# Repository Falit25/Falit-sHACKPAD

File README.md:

# Falit'sHackpad – 10-Key Macro Pad

Falit's Hackpad is a custom 10-key macro pad built using a XIAO RP2040 DIP board.
It uses KMK firmware (CircuitPython) and is designed for productivity shortcuts like launching apps, switching desktops, and system controls.

---

## Features

* 10 mechanical keys
* 4× SK6812 RGB LEDs
* XIAO RP2040 DIP controller
* USB-C connection
* KMK firmware
* Custom 3D-printed case
* App-launch and system macros (Windows)

---

## Hardware

* Controller: Seeed XIAO RP2040 DIP
* Switches: MX-style mechanical switches
* LEDs: SK6812 Mini (NeoPixel-compatible)
* PCB: Custom KiCad design
* Case: Custom Fusion 360 model
* Connection: USB-C

---

## Firmware

Firmware is written using **KMK** and runs on **CircuitPython**.

### Steps

1. Install CircuitPython on XIAO RP2040
2. Copy the KMK firmware folder to the board
3. Upload `main.py` to the CIRCUITPY drive
4. Reboot the board

---

## Notes

* App-launch shortcuts use AutoHotkey for reliability
* LEDs are driven from GPIO3
* Keys are connected using direct GPIO pins
* Modify `main.py` to change macros or lighting behavior

---

## License

This project is for personal and educational use.

---

## Author

Mahi
B.Tech Student – VIT Bhopal
Specialization: AI & ML

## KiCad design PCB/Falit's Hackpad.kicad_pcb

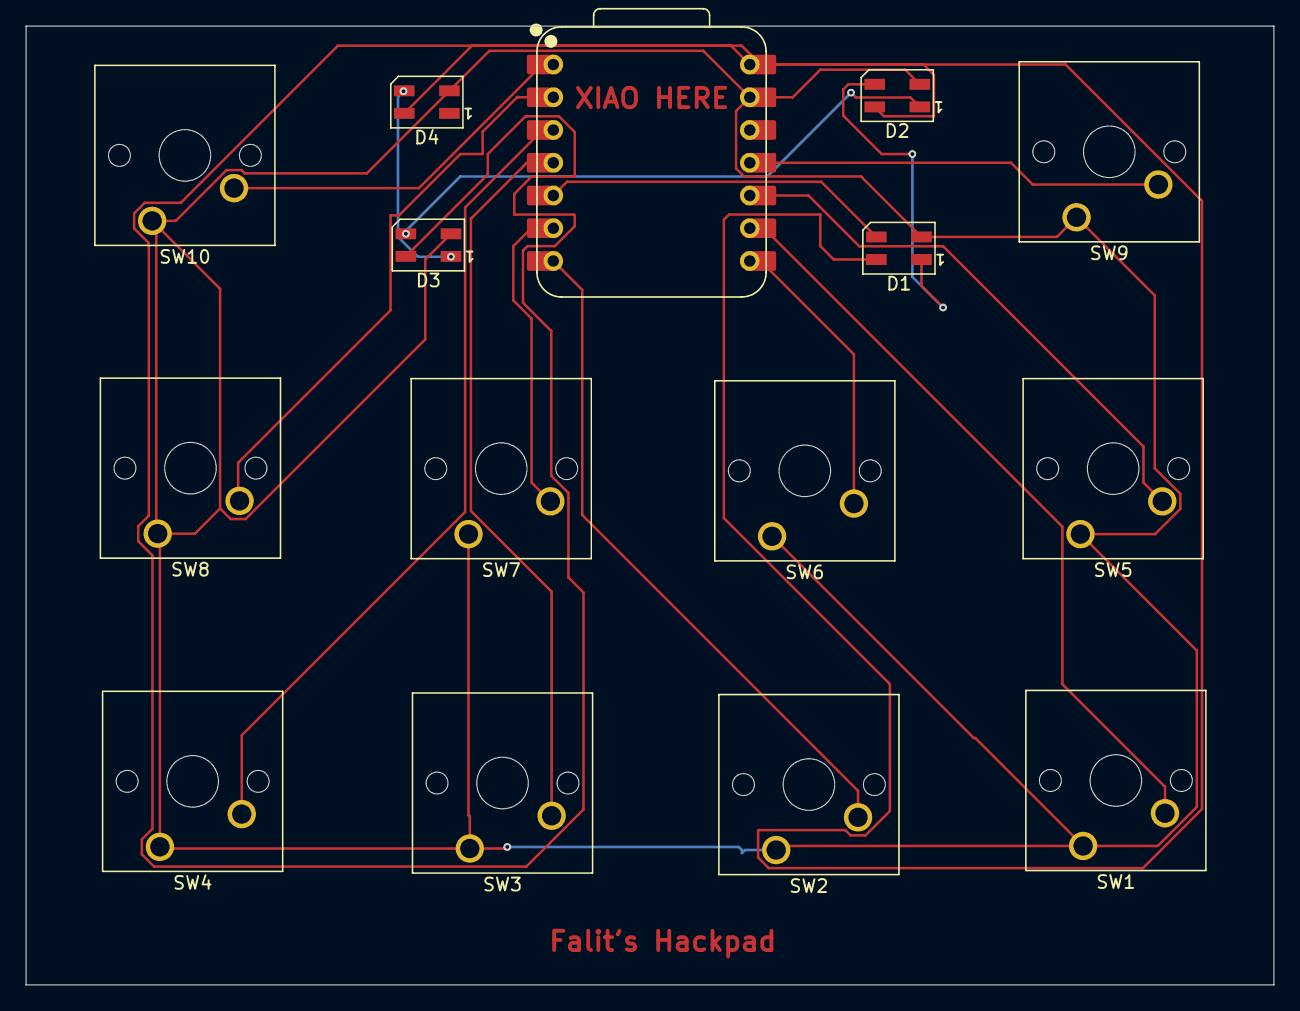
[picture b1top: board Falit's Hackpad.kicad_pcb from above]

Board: 2 copper layers, 96.8 x 74.4 mm, 15 parts (0 on the bottom side), 16 nets.

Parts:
D1, D2, D3, D4: SK6812MINI; LED_SK6812MINI_PLCC4_3.5x3.5mm_P1.75mm
SW1, SW2, SW3, SW4, SW5, SW6, SW7, SW8, SW9, SW10: SW_Push; SW_Cherry_MX_1.00u_PCB
U1: XIAO-RP2040-DIP

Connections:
+5V: D1.4 (VDD), D2.4 (VDD), D3.4 (VDD), D4.4 (VDD), U1.14 (VBUS)
GND: D1.2 (VSS), D2.2 (VSS), D3.2 (VSS), D4.2 (VSS), SW1.1, SW2.1, SW3.1, SW4.1, SW5.1, SW6.1, SW7.1, SW8.1, SW9.1, SW10.1, U1.13 (GND)
unnamed: D1.3 (DIN), U1.5 (GPIO6/SDA)
unnamed: D1.1 (DOUT), D2.3 (DIN)
unnamed: D2.1 (DOUT), D3.3 (DIN)
unnamed: D3.1 (DOUT), D4.3 (DIN)
unnamed: SW2.2, U1.7 (GPIO0/TX)
unnamed: SW6.2, U1.8 (GPIO1/RX)
unnamed: SW1.2, U1.9 (GPIO2/SCK)
unnamed: SW9.2, U1.11 (GPIO3/MOSI)
unnamed: SW5.2, U1.10 (GPIO4/MISO)
unnamed: SW7.2, U1.6 (GPIO7/SCL)
unnamed: SW10.2, U1.1 (GPIO26/ADC0/A0)
unnamed: SW8.2, U1.2 (GPIO27/ADC1/A1)
unnamed: SW4.2, U1.3 (GPIO28/ADC2/A2)
unnamed: SW3.2, U1.4 (GPIO29/ADC3/A3)

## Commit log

2026-01-23 Expand README with features and setup instructions
    Added detailed sections on features, hardware, firmware installation steps, notes, license, and author information.
